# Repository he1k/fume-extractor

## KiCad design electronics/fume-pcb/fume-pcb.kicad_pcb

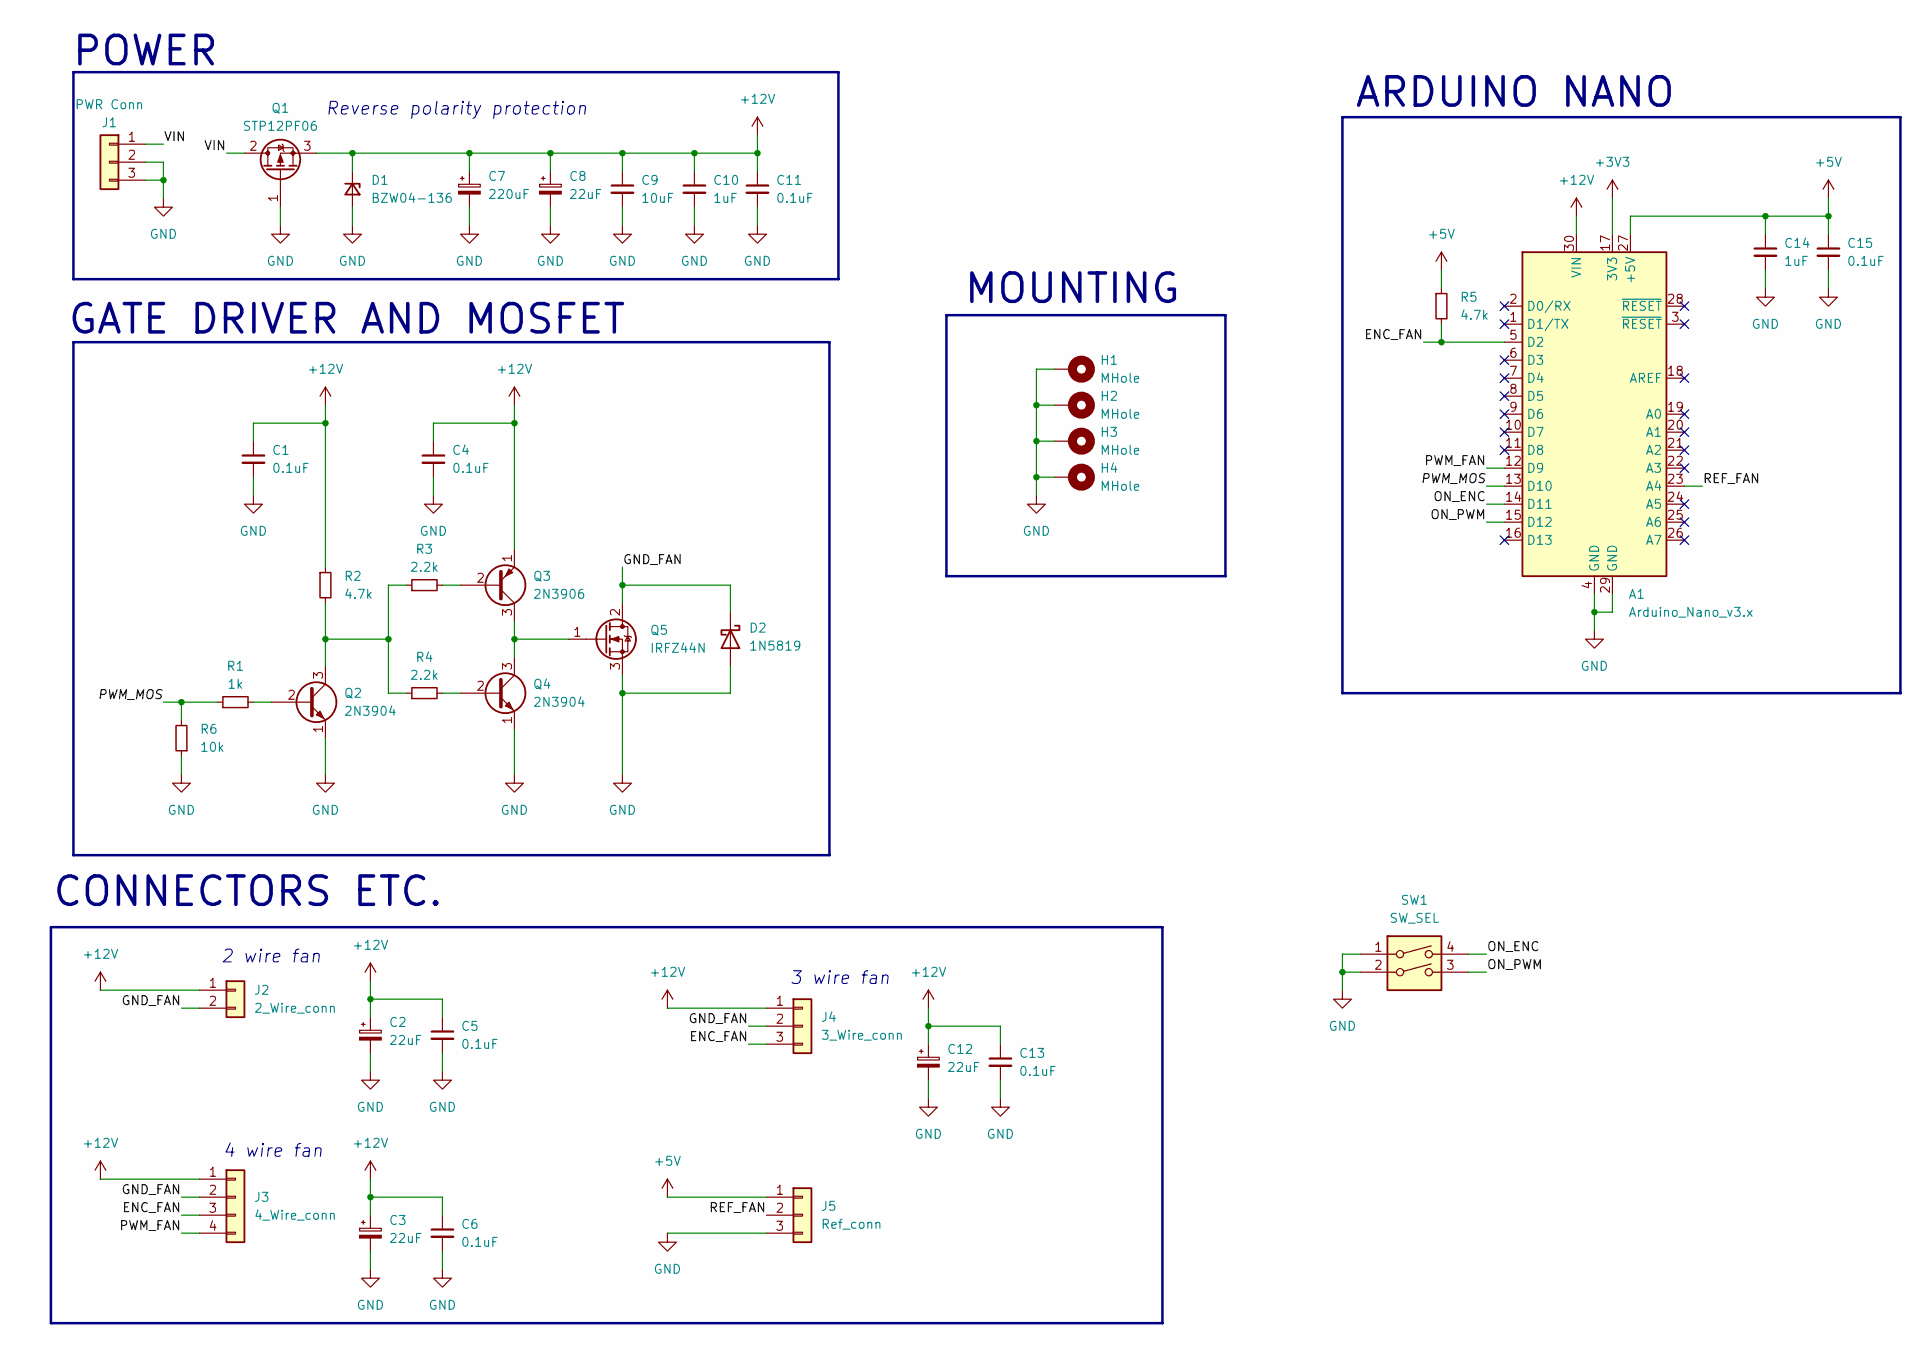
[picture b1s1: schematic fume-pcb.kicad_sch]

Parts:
A1: Arduino_Nano_v3.x; Arduino_Nano
C1, C4, C5, C6, C11, C13, C15: 0.1uF; C_Disc_D5.0mm_W2.5mm_P5.00mm
C2, C3, C8, C12: 22uF; CP_Radial_D4.0mm_P2.00mm
C7: 220uF; CP_Radial_D6.3mm_P2.50mm
C9: 10uF; C_Disc_D5.0mm_W2.5mm_P5.00mm
C10, C14: 1uF; C_Disc_D5.0mm_W2.5mm_P5.00mm
D1: BZW04-136; D_DO-15_P10.16mm_Horizontal
D2: 1N5819; D_DO-41_SOD81_P10.16mm_Horizontal
H1, H2, H3, H4: MHole; MountingHole_3.2mm_M3_Pad_Via
J1: PWR Conn; BarrelJack_Horizontal
J2: 2_Wire_conn; JST_XH_B2B-XH-A_1x02_P2.50mm_Vertical
J3: 4_Wire_conn; JST_XH_B4B-XH-A_1x04_P2.50mm_Vertical
J4: 3_Wire_conn; JST_XH_B3B-XH-A_1x03_P2.50mm_Vertical
J5: Ref_conn; JST_XH_B3B-XH-A_1x03_P2.50mm_Vertical
Q1: STP12PF06; TO-220-3_Vertical
Q2, Q4: 2N3904; TO-92_Inline
Q3: 2N3906; TO-92_Inline
Q5: IRFZ44N; TO-220-3_Vertical
R1: 1k; R_Axial_DIN0207_L6.3mm_D2.5mm_P10.16mm_Horizontal
R2, R5: 4.7k; R_Axial_DIN0207_L6.3mm_D2.5mm_P10.16mm_Horizontal
R3, R4: 2.2k; R_Axial_DIN0207_L6.3mm_D2.5mm_P10.16mm_Horizontal
R6: 10k; R_Axial_DIN0207_L6.3mm_D2.5mm_P10.16mm_Horizontal
SW1: SW_SEL; SW_DIP_SPSTx02_Slide_6.7x6.64mm_W7.62mm_P2.54mm_LowProfile

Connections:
+3V3: A1.17 (3V3)
+5V: A1.27 (+5V), C14.1, C15.1, J5.1, R5.1
+12V: A1.30 (VIN), C1.1, C2.1, C3.1, C4.1, C5.1, C6.1, C7.1, C8.1, C9.1, C10.1, C11.1, C12.1, C13.1, D1.1 (K), J2.1, J3.1, J4.1, Q1.3 (S), Q3.1 (E), R2.1
/ENC_FAN: A1.5 (D2), J3.3, J4.3, R5.2
/GND_FAN: D2.1 (K), J2.2, J3.2, J4.2, Q5.2 (D)
/ON_ENC: A1.14 (D11), SW1.4
/ON_PWM: A1.15 (D12), SW1.3
/PWM_FAN: A1.12 (D9), J3.4
/PWM_MOS: A1.13 (D10), R1.1, R6.2
/REF_FAN: A1.23 (A4), J5.2
/VIN: J1.1, Q1.2 (D)
GND: A1.4 (GND), A1.29 (GND), C1.2, C2.2, C3.2, C4.2, C5.2, C6.2, C7.2, C8.2, C9.2, C10.2, C11.2, C12.2, C13.2, C14.2, C15.2, D1.2 (A), D2.2 (A), H1.1, H2.1, H3.1, H4.1, J1.2, J1.3, J5.3, Q1.1 (G), Q2.1 (E), Q4.1 (E), Q5.3 (S), R6.1, SW1.1, SW1.2
unnamed: Q2.2 (B), R1.2
unnamed: Q2.3 (C), R2.2, R3.1, R4.1
unnamed: Q3.2 (B), R3.2
unnamed: Q3.3 (C), Q4.3 (C), Q5.1 (G)
unnamed: Q4.2 (B), R4.2

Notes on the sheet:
4 wire fan
CONNECTORS ETC.
3 wire fan
2 wire fan
ARDUINO NANO
POWER
GATE DRIVER AND MOSFET
MOUNTING
Reverse polarity protection

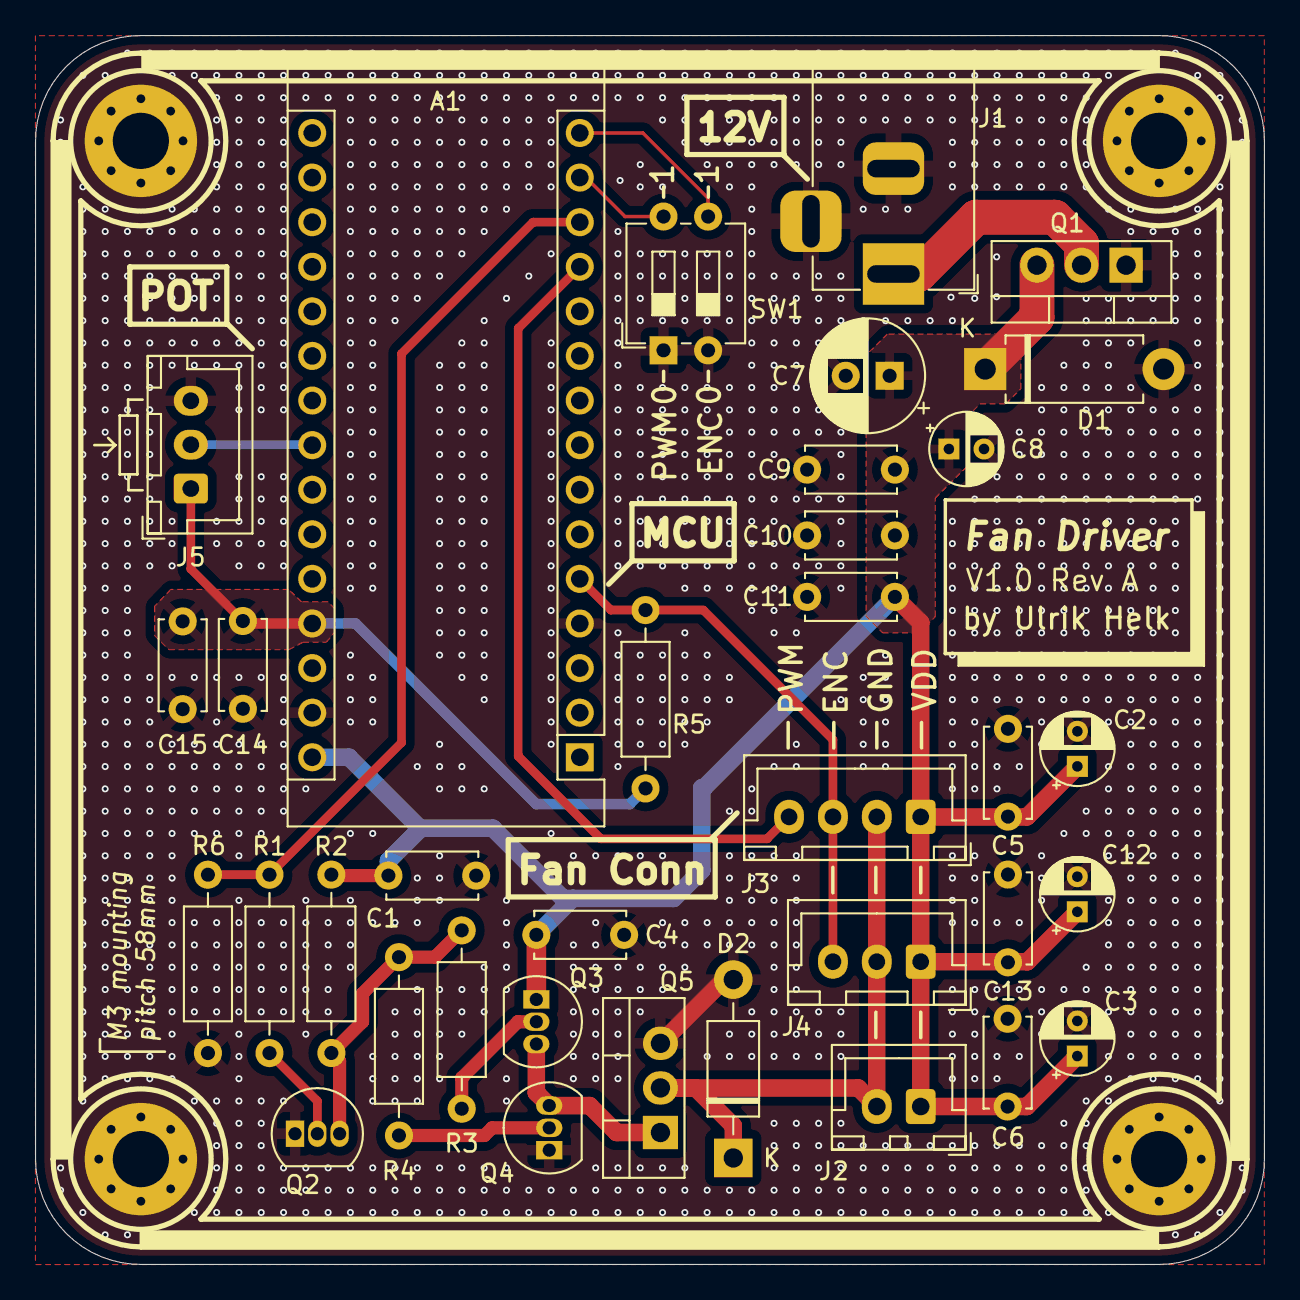
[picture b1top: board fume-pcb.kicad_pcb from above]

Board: 2 copper layers, 70.0 x 70.0 mm, 39 parts (0 on the bottom side), 16 nets.

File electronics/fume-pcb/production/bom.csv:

Designator,Footprint,Quantity,Value,LCSC Part #
A1,Arduino_Nano,1,Arduino_Nano_v3.x,
"C1, C11, C13, C15, C4, C5, C6",C_Disc_D5.0mm_W2.5mm_P5.00mm,7,0.1uF,
"C10, C14",C_Disc_D5.0mm_W2.5mm_P5.00mm,2,1uF,
"C12, C2, C3, C8",CP_Radial_D4.0mm_P2.00mm,4,22uF,
C7,CP_Radial_D6.3mm_P2.50mm,1,220uF,
C9,C_Disc_D5.0mm_W2.5mm_P5.00mm,1,10uF,
D1,D_DO-15_P10.16mm_Horizontal,1,BZW04-136,
D2,D_DO-41_SOD81_P10.16mm_Horizontal,1,1N5819,
J1,BarrelJack_Horizontal,1,PWR Conn,
J2,JST_XH_B2B-XH-A_1x02_P2.50mm_Vertical,1,2_Wire_conn,
J3,JST_XH_B4B-XH-A_1x04_P2.50mm_Vertical,1,4_Wire_conn,
J4,JST_XH_B3B-XH-A_1x03_P2.50mm_Vertical,1,3_Wire_conn,
J5,JST_XH_B3B-XH-A_1x03_P2.50mm_Vertical,1,Ref_conn,
Q1,TO-220-3_Vertical,1,STP12PF06,
"Q2, Q4",TO-92_Inline,2,2N3904,
Q3,TO-92_Inline,1,2N3906,
Q5,TO-220-3_Vertical,1,IRFZ44N,
R1,R_Axial_DIN0207_L6.3mm_D2.5mm_P10.16mm_Horizontal,1,1k,
"R2, R5",R_Axial_DIN0207_L6.3mm_D2.5mm_P10.16mm_Horizontal,2,4.7k,
"R3, R4",R_Axial_DIN0207_L6.3mm_D2.5mm_P10.16mm_Horizontal,2,2.2k,
R6,R_Axial_DIN0207_L6.3mm_D2.5mm_P10.16mm_Horizontal,1,10k,
SW1,SW_DIP_SPSTx02_Slide_6.7x6.64mm_W7.62mm_P2.54mm_LowProfile,1,SW_SEL,

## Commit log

2025-02-25 init
2025-03-04 Almost done with PCB
2025-03-05 PCB ORDERED
